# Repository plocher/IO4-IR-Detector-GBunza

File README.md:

# IO4-IR-Detector-GBunza
## License: CERN Open Hardware Licence v1.2

IO4 Quad Optical/IR Detector baseboard

Derived from Geoff Bunza's SMA Detector, published in his column in MRH as "SMA23 – A New DCC & DC Car & Loco Detector – Differential Absolute Position Detector (DAPD)"

This version eschews "small" in favor of a remote mountable IO4 baseboard that can be mounted near the point of use, and then use [sensors disguised as ties](/pages/IO4-IR-Detector-GBunza-Fingers.html) for the sensor electronics themselves.

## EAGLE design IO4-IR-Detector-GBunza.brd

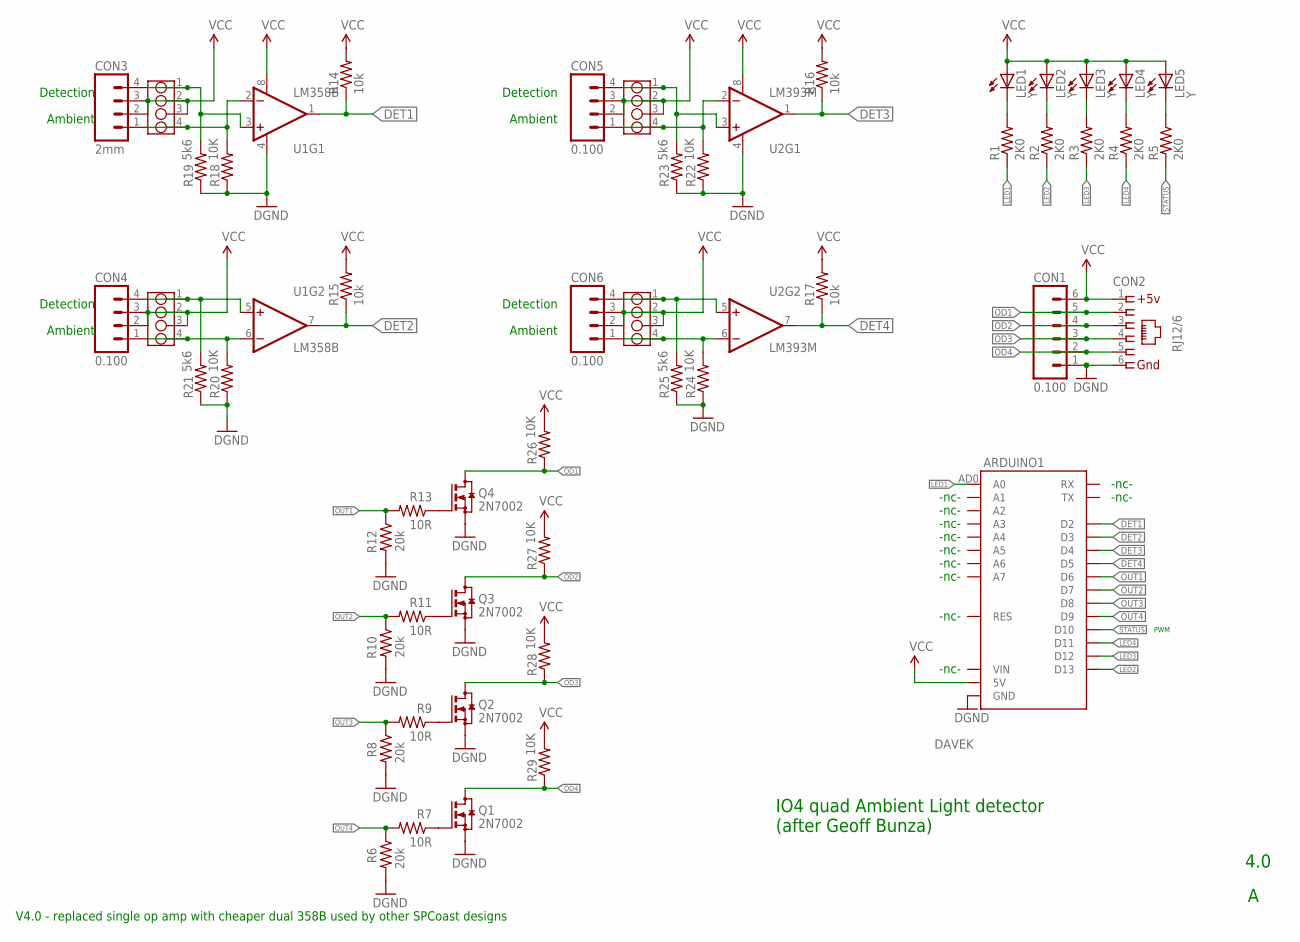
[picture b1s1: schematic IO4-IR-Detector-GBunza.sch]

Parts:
ARDUINO1: DAVEK; ARDUINO_PRO_MINI_DAVEK
CON1: 0.100; 1X06_LOCK
CON2: RJ12/6; RJ25-INVERTED
CON3: 2mm; 1X04_LOCK
CON4, CON5, CON6: 0.100; 1X04_LOCK
DET1, DET2, DET3, DET4: 2mm; 4P-2.0
LED1, LED2, LED3, LED4, LED5: Y; 0603-LED
Q1, Q2, Q3, Q4: 2N7002; SOT23
R1, R2, R3, R4, R5: 2K0; 0603-RES
R6, R8, R10, R12: 20k; 0603-RES
R7, R9, R11, R13: 10R; 0603-RES
R14, R15, R16, R17: 10k; 0603-RES
R18, R20, R22, R24, R26, R27, R28, R29: 10K; 0603-RES
R19, R21, R23, R25: 5k6; 0603-RES
U1: LM358B; SO08
U2: LM393M; SO08

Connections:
DET1: ARDUINO1.D2, R14.1, U1.1 (OUT)
DET2: ARDUINO1.D3, R15.1, U1.7 (OUT)
DET3: ARDUINO1.D4, R16.1, U2.1 (OUT)
DET4: ARDUINO1.D5, R17.1, U2.7 (OUT)
GND: ARDUINO1.GND@1 (GND), ARDUINO1.GND@2 (GND), ARDUINO1.GND@4 (GND), CON1.1, CON2.6, Q1.2 (S), Q2.2 (S), Q3.2 (S), Q4.2 (S), R6.2, R8.2, R10.2, R12.2, R18.1, R19.1, R20.1, R21.1, R22.1, R23.1, R24.1, R25.1, U1.4 (V-), U2.4 (V-)
LED1: ARDUINO1.AD0 (A0), R1.1
LED2: ARDUINO1.D13, R2.1
LED3: ARDUINO1.D12, R3.1
LED4: ARDUINO1.D11, R4.1
unnamed: LED5.C, R5.1
unnamed: LED4.C, R4.2
unnamed: LED3.C, R3.2
unnamed: LED2.C, R2.2
unnamed: LED1.C, R1.2
unnamed: CON3.1, DET1.4, R18.2, U1.2 (-IN)
unnamed: CON4.1, DET2.4, R20.2, U1.6 (-IN)
unnamed: CON4.4, DET2.1, R21.2, U1.5 (+IN)
unnamed: CON5.1, DET3.4, R22.2, U2.2 (-IN)
unnamed: CON5.4, DET3.1, R23.2, U2.3 (+IN)
unnamed: CON6.1, DET4.4, R24.2, U2.6 (-IN)
unnamed: CON6.4, DET4.1, R25.2, U2.5 (+IN)
unnamed: Q4.1 (G), R13.1
unnamed: CON3.4, DET1.1, R19.2, U1.3 (+IN)
unnamed: Q3.1 (G), R11.1
unnamed: Q2.1 (G), R9.1
unnamed: Q1.1 (G), R7.1
OD1: CON1.5, CON2.2, Q4.3 (D), R26.1
OD2: CON1.4, CON2.3, Q3.3 (D), R27.1
OD3: CON1.3, CON2.4, Q2.3 (D), R28.1
OD4: CON1.2, CON2.5, Q1.3 (D), R29.1
OUT1: ARDUINO1.D6, R12.1, R13.2
OUT2: ARDUINO1.D7, R10.1, R11.2
OUT3: ARDUINO1.D8, R8.1, R9.2
OUT4: ARDUINO1.D9, R6.1, R7.2
STATUS: ARDUINO1.D10, R5.2
VCC: ARDUINO1.5V, CON1.6, CON2.1, CON3.2, CON3.3, CON4.2, CON4.3, CON5.2, CON5.3, CON6.2, CON6.3, DET1.2, DET1.3, DET2.2, DET2.3, DET3.2, DET3.3, DET4.2, DET4.3, LED1.A, LED2.A, LED3.A, LED4.A, LED5.A, R14.2, R15.2, R16.2, R17.2, R26.2, R27.2, R28.2, R29.2, U1.8 (V+), U2.8 (V+)

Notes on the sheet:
IO4 quad Ambient Light detector (after Geoff Bunza)
4.0
Detection
Ambient
PWM
-nc-
V4.0 - replaced single op amp with cheaper dual 358B used by other SPCoast designs

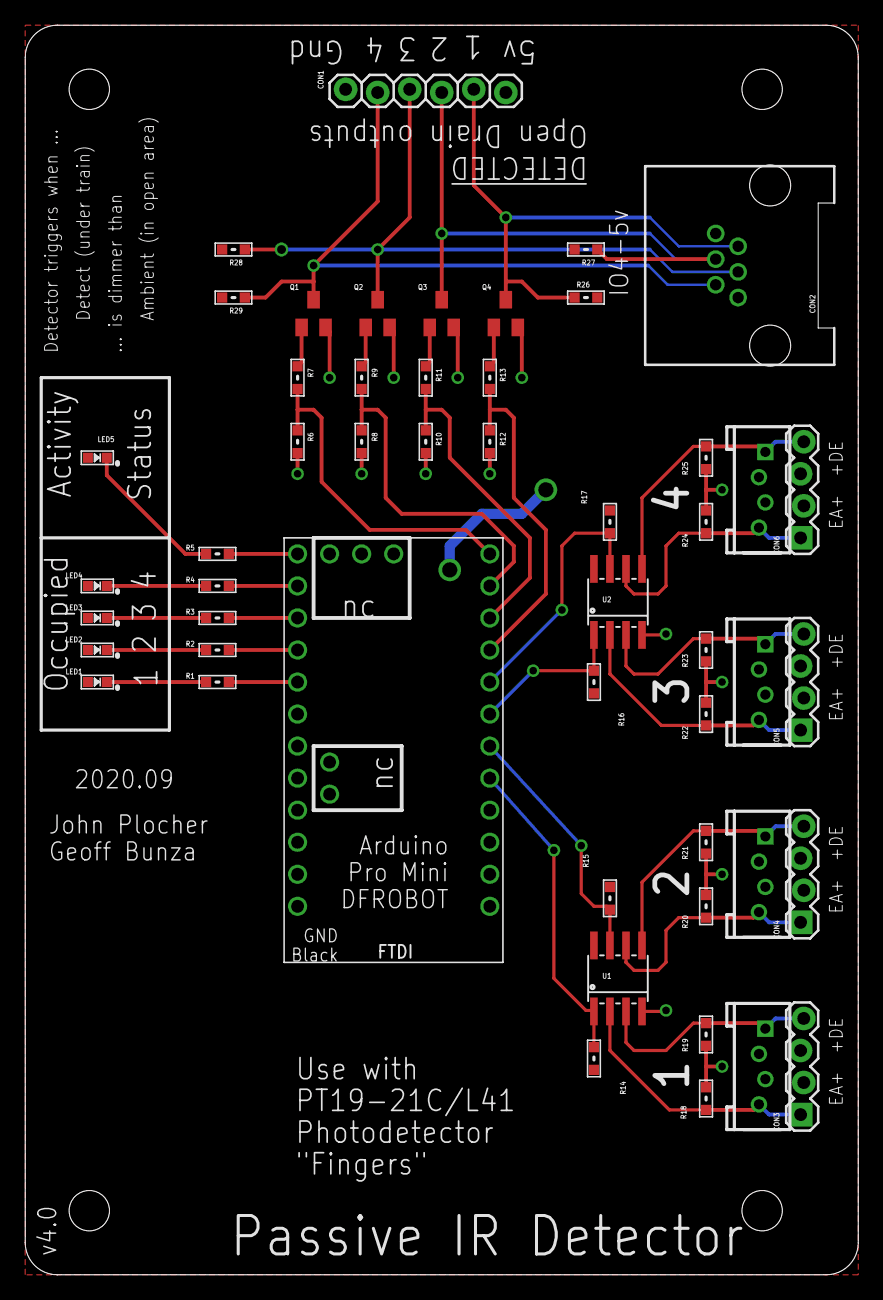
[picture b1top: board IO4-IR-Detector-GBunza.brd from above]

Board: 2 copper layers, 66.0 x 99.1 mm, 51 parts (0 on the bottom side), 36 nets.

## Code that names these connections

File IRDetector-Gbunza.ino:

#define DET1  2
#define DET2  3
#define DET3  4
#define DET4  5
#define OUT1  6
#define OUT2  7
#define OUT3  8
#define OUT4  9
#define LED1  13
#define LED2  12
#define LED3  11
#define LED4  10

#define HYSTERESIS (long)2000    // in mS units, 2000 = 2.0 seconds

#define OCCUPIED LOW
#define EMPTY    ~OCCUPIED


#define smillis() ((long)millis())

class Detector {
public:
    Detector(int number, int det, int out, int led) {
      init(number, det, out, led);
    }
    
    Detector(void) {
        num       = -1;
        detPin    = -1;
        outPin    = -1;
        ledPin    = -1;
        delaytime = smillis();
        detected  = false;
    }
    
    void init(int number, int det, int out, int led) {
        num       = number;  // 1..4
        detPin    = det;
        outPin    = out;
        ledPin    = led;
        detected  = false;   // default to unoccupied...
        delaytime = smillis();  // expired...
        pinMode(ledPin,     OUTPUT);
        pinMode(outPin,     OUTPUT);
        pinMode(detPin,     INPUT);
        digitalWrite(outPin, detected ? OCCUPIED : EMPTY); 
        digitalWrite(ledPin, detected ? LOW : HIGH); 
    }
    
    boolean after(long timeout) {
        return smillis()-timeout>0;
    }

    boolean check(void) {
        if (num == -1) return false;
      
        int r1 =  digitalRead(detPin);
        if (r1 == HIGH) {
            detected = true;
            delaytime = smillis() + HYSTERESIS;  // expiration time is pushed out every time detection is seen
        }
        // hysteresis expired without further detection events
        if (after(delaytime)) {
            detected = false;
        }
        // report occupancy...
        digitalWrite(outPin, detected ? OCCUPIED : EMPTY); 
        digitalWrite(ledPin, detected ? LOW : HIGH); 
        return detected;
    }
    
private:  
    int      num;
    long     delaytime;
    boolean  detected;
    int      detPin;
    int      outPin;
    int      ledPin;
};


Detector circuit0(0, DET1, OUT1, LED1);
Detector circuit1(1, DET2, OUT2, LED2);
Detector circuit2(2, DET3, OUT3, LED3);
Detector circuit3(3, DET4, OUT4, LED4);

void setup() {
}

void loop() {
    circuit0.check();
    circuit1.check();
    circuit2.check();
    circuit3.check();
}

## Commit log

2019-11-25 Added more detail
2019-11-26 highlighter tag is cpp, not C++
2019-12-07 updated sketch
2019-12-09 added graphic
2020-05-04 updated tags
2020-09-23 changed from expensive TL331 to inexpensive LM258/LM358
2020-09-24 added V4 changes note to sch
2020-09-24 op-amp value changed to LM358B
2020-10-06 normalized values
2022-02-23 Vscore changed to mouse bites, larger

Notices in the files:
parts and their libraries:
SparkFun-Aesthetics: Licensing: Creative Commons ShareAlike 4.0 International - https://creativecommons.org/licenses/by-sa/4.0
